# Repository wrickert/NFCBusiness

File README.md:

# NFCBusiness
## Overview
In order to stand out to potential employers I wanted to create my own variation on the PCB business card. I wanted my badge to do more than just look intresting. However, batteries are bulky and expensive. With the sheer number of phones equiped with Google pay/apple pay NFC in phones is becoming increasingly common. I think this makes NFC equiped PCB business cards a natural combination.

## RF430
This project uses a clever little chip, the RF430FRL154HCRGER. This chip is a variant on TI's MSP430. This one combines a NFC RF front end with a MSP430. We will be programming with a JTAG header and I will be building an accompanying POGO pin programming jig.

## D6 CharliePlexing Variant
There is a way to use CharliePlexing to drive seven LEDs with only two GPIO. This does not give you control of individual LEDs, but works in convient pairs for displaying dice values.<br>

## Programming Jig
Created a programming Jig that uses POGO pins, https://www.digikey.com/product-detail/en/mill-max-manufacturing-corp/0906-0-15-20-76-14-11-0/ED8180-ND <br>
This consists of two different PCBs that can all be stacked to reach the desired result<br>

## Status
1Jan2019 - Completed and ordered version 1<br>
17Jan2019 - IT WORKS! While the antenna leaves much to be desired it is good enough to register on my phone! Need to improve antenna and create programming jig.<br>
18Jan2019 - Fixed issues, created new PCB antenna, ordered version 2<br>
19Jan2019 - Found issue with V2, created V2a. Completed V1 Programming Jig and ordered from JLCPCB.<br>

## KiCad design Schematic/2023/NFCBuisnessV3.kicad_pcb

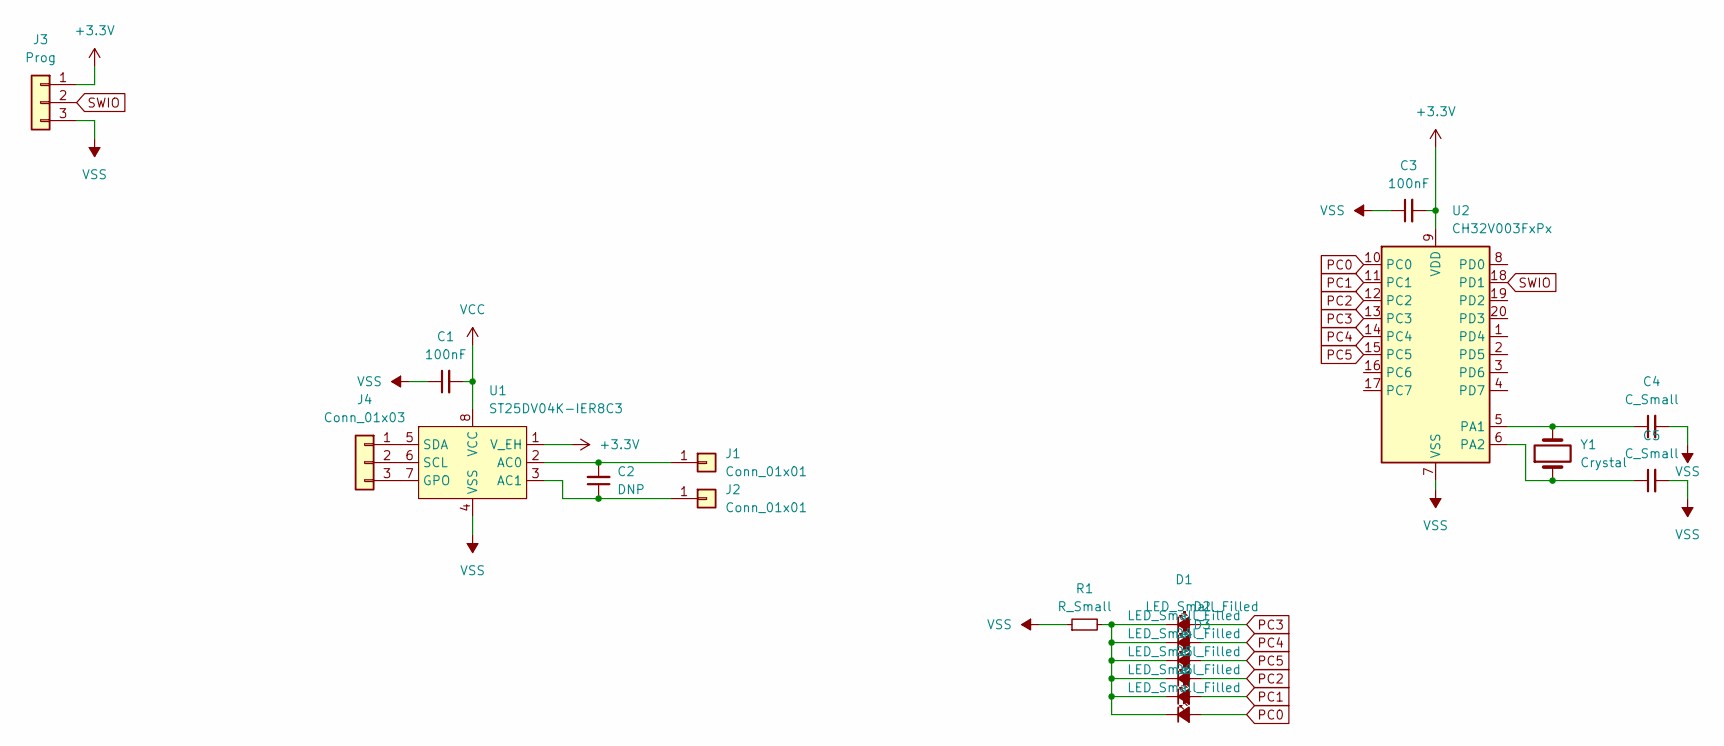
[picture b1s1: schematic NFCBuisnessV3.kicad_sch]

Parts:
C1, C3: 100nF; C_0805_2012Metric
C2: DNP; C_0805_2012Metric
C4, C5: C_Small; C_0805_2012Metric
D1, D2, D3, D4, D5, D6: LED_Small_Filled; LED_0805_2012Metric
J1, J2: Conn_01x01; NFCadapter
J3: Prog; PinHeader_1x03_P2.54mm_Vertical
J4: Conn_01x03; PinHeader_1x03_P2.54mm_Vertical
R1: R_Small; R_0805_2012Metric
U1: ST25DV04K-IER8C3; TSSOP_K-IER6T3_STM
U2: CH32V003FxPx; TSSOP-20_4.4x6.5mm_P0.65mm
Y1: Crystal; Crystal_SMD_2012-2Pin_2.0x1.2mm_HandSoldering

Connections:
+3.3V: C3.2, J3.1, U1.1 (V_EH), U2.9 (VDD)
unnamed: D1.1 (K), D2.1 (K), D3.1 (K), D4.1 (K), D5.1 (K), D6.1 (K), R1.2
unnamed: C2.2, J1.1, U1.2 (AC0)
unnamed: C2.1, J2.1, U1.3 (AC1)
unnamed: J4.1, U1.5 (SDA)
unnamed: J4.2, U1.6 (SCL)
unnamed: J4.3, U1.7 (GPO)
unnamed: C4.1, U2.5 (PA1), Y1.2
unnamed: C5.1, U2.6 (PA2), Y1.1
PC0: D6.2 (A), U2.10 (PC0)
PC1: D5.2 (A), U2.11 (PC1)
PC2: D4.2 (A), U2.12 (PC2)
PC3: D1.2 (A), U2.13 (PC3)
PC4: D2.2 (A), U2.14 (PC4)
PC5: D3.2 (A), U2.15 (PC5)
SWIO: J3.2, U2.18 (PD1)
VCC: C1.2, U1.8 (VCC)
VSS: C1.1, C3.1, C4.2, C5.2, J3.3, R1.1, U1.4 (VSS), U2.7 (VSS)

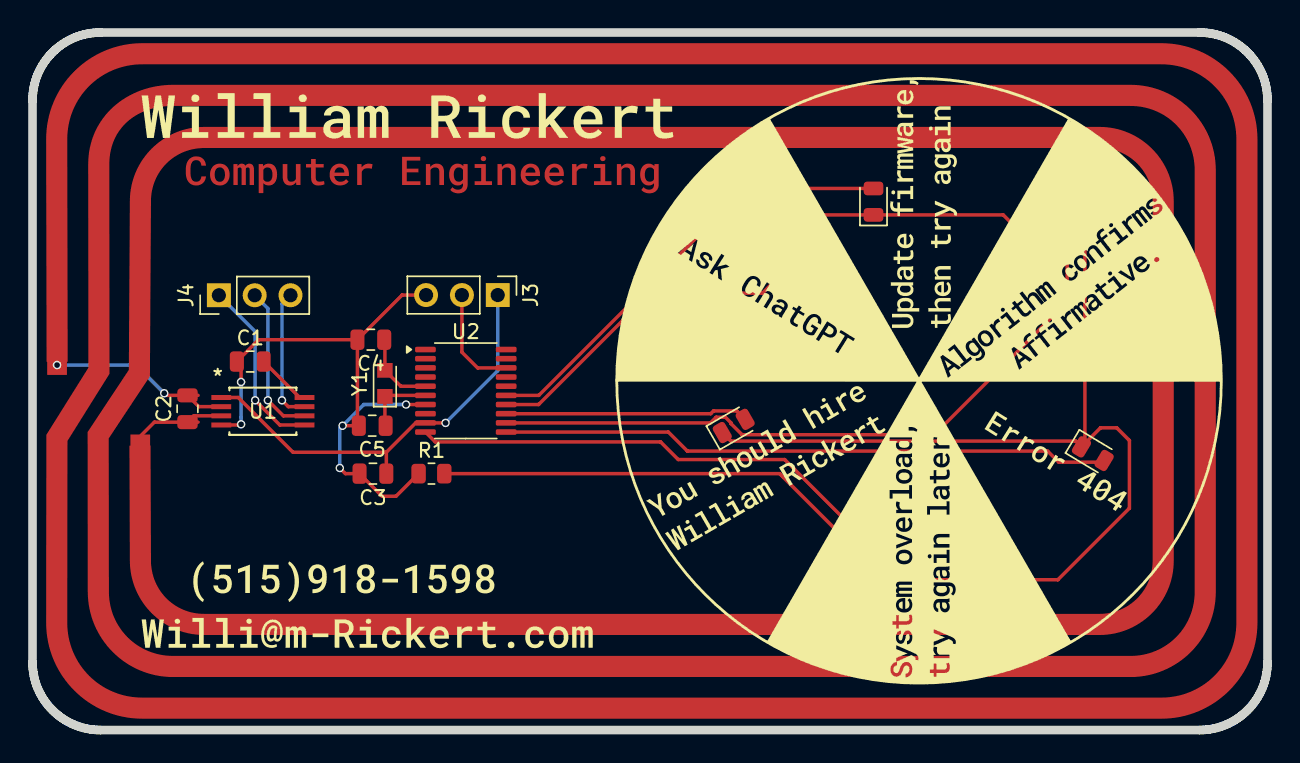
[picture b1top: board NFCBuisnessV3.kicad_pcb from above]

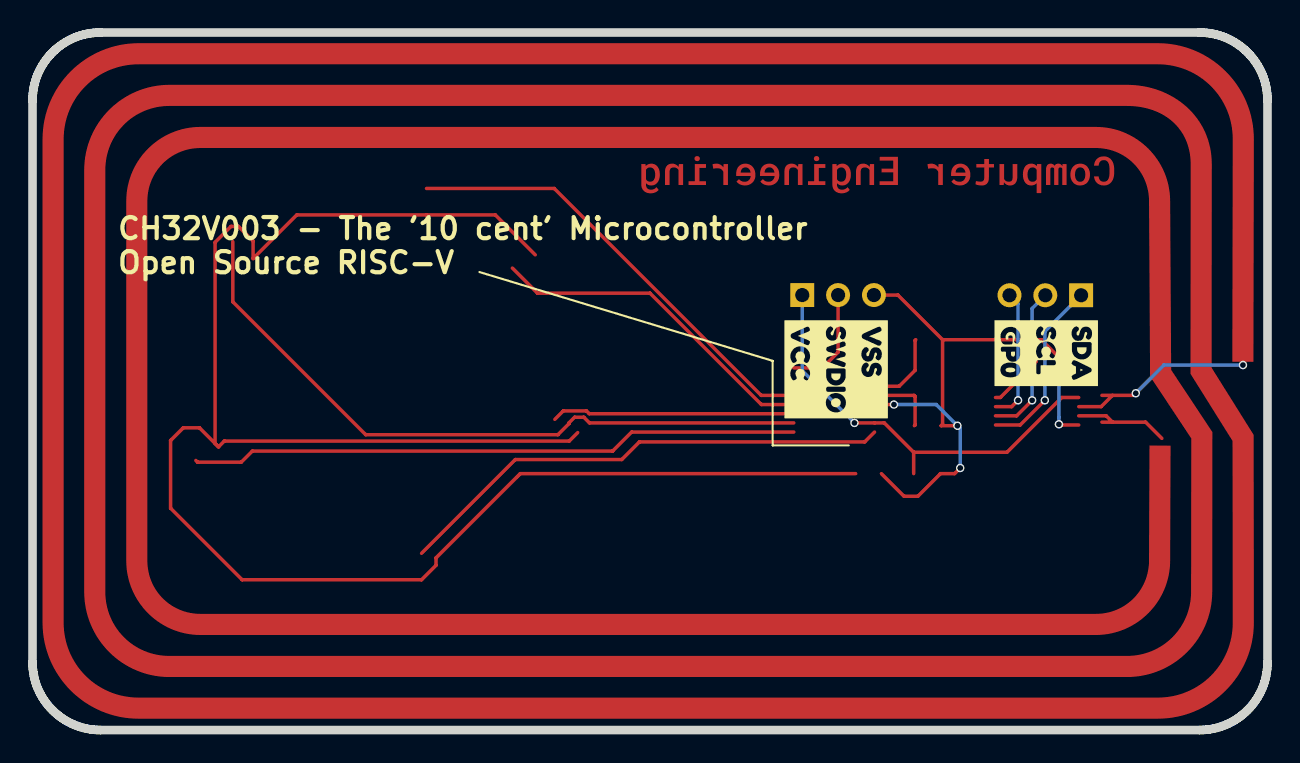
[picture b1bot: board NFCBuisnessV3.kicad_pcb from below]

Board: 2 copper layers, 87.6 x 49.5 mm, 21 parts (2 on the bottom side), 18 nets.

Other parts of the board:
kibuzzard-65E89835: G***; kibuzzard-65E89835
kibuzzard-65F9F6C6: G***; kibuzzard-65F9F6C6

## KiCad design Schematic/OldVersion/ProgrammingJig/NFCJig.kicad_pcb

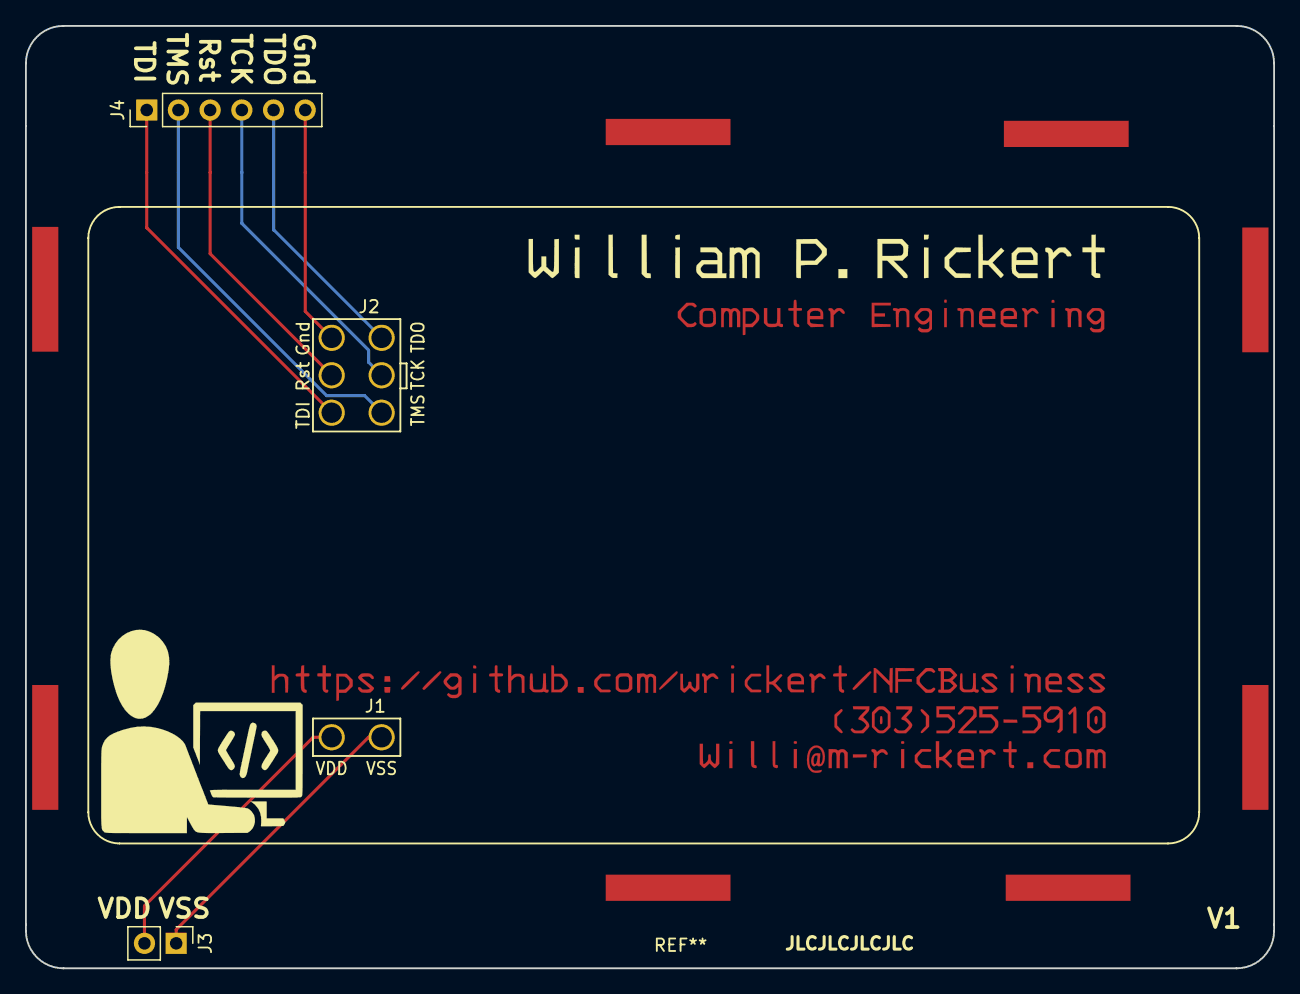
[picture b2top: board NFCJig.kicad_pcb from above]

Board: 2 copper layers, 100.0 x 75.5 mm, 4 parts (0 on the bottom side), 8 nets.

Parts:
J1: Power; PogoPwr
J2: JTAG; PogoJTAG
J3: Power; Pin_Header_Straight_1x02_Pitch2.54mm
J4: JTAG; Pin_Header_Straight_1x06_Pitch2.54mm

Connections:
unnamed: J1.1, J3.1
unnamed: J1.2, J3.2
unnamed: J2.1, J4.1
unnamed: J2.2, J4.2
unnamed: J2.3, J4.3
unnamed: J2.4, J4.4
unnamed: J2.5, J4.6
unnamed: J2.6, J4.5

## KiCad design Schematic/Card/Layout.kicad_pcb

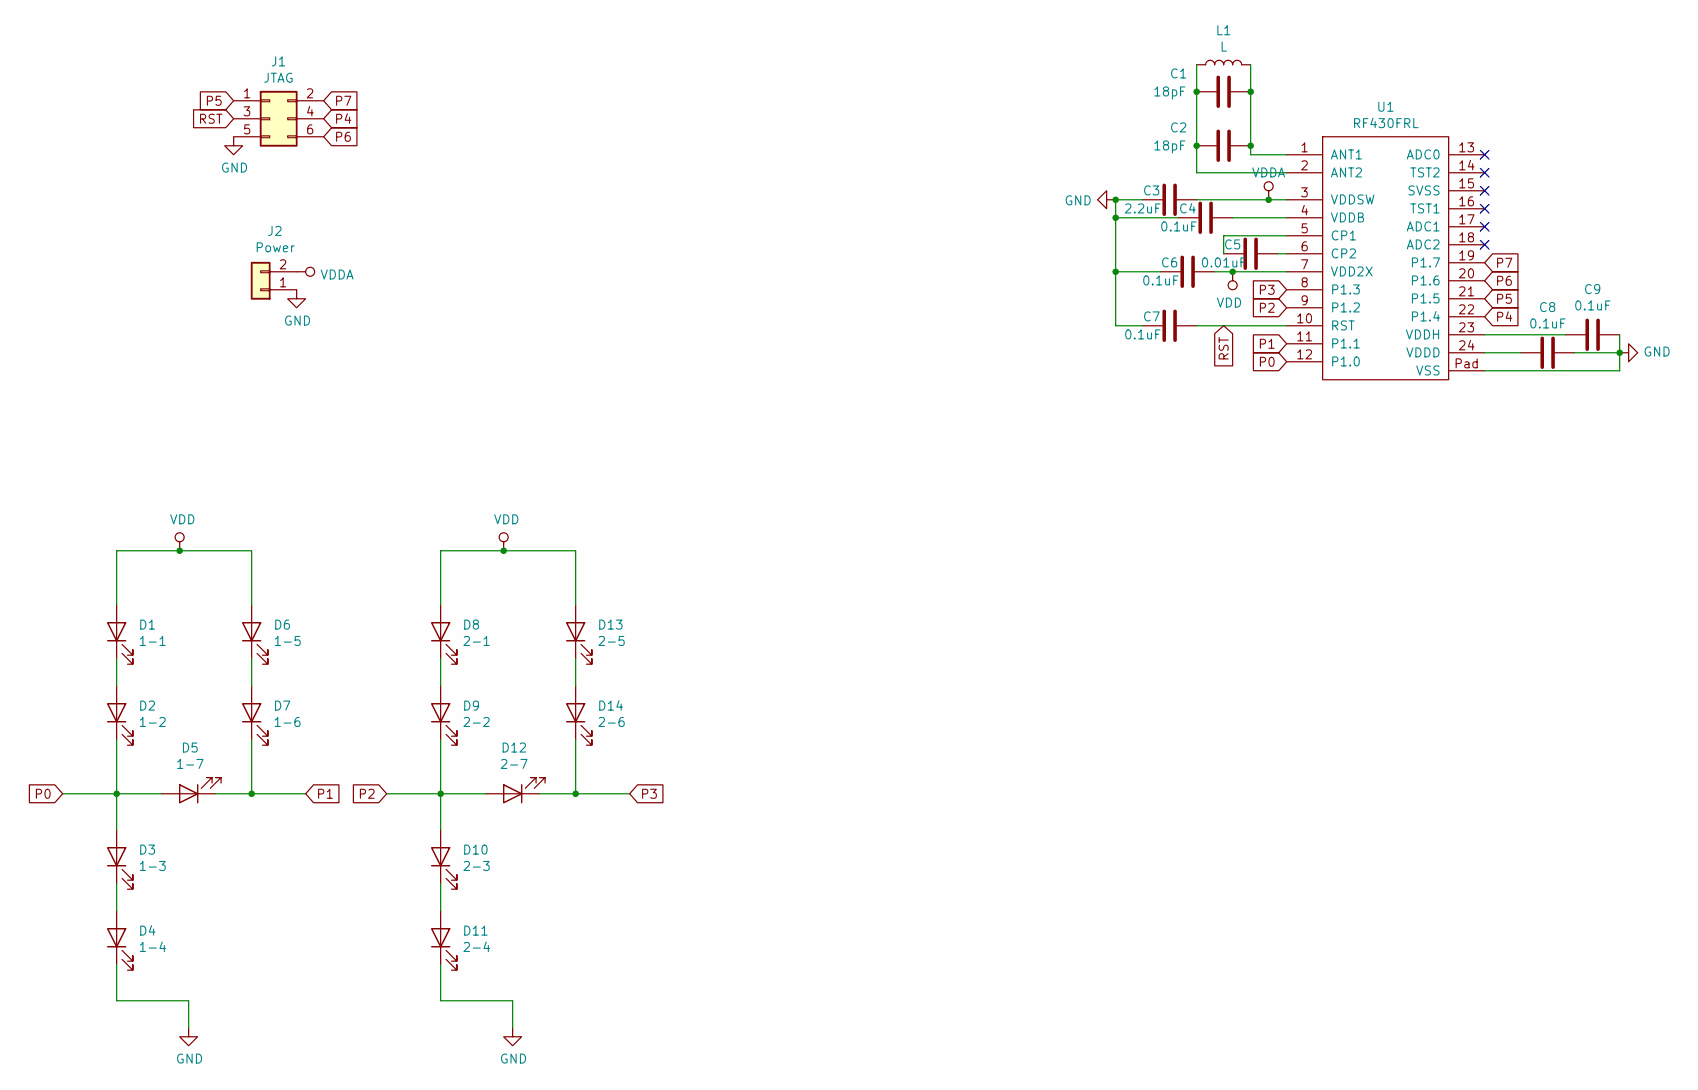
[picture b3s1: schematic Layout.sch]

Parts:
C1, C2: 18pF; C_0805
C3: 2.2uF; C_0805
C4, C6, C7, C8, C9: 0.1uF; C_0805
C5: 0.01uF; C_0805
D1: 1-1; LED_0805
D2: 1-2; LED_0805
D3: 1-3; LED_0805
D4: 1-4; LED_0805
D5: 1-7; LED_0805
D6: 1-5; LED_0805
D7: 1-6; LED_0805
D8: 2-1; LED_0805
D9: 2-2; LED_0805
D10: 2-3; LED_0805
D11: 2-4; LED_0805
D12: 2-7; LED_0805
D13: 2-5; LED_0805
D14: 2-6; LED_0805
J1: JTAG; Jtag
J2: Power; PwrPins
L1: L; Layout
U1: RF430FRL; QFN-24-1EP_4x4mm_Pitch0.5mm

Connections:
GND: C3.2, C4.2, C6.2, C7.2, C8.1, C9.1, D4.1 (K), D11.1 (K), J1.5, J2.1, U1.14 (TST2), U1.16 (TST1), U1.25, U1.Pad (VSS); also elsewhere on the board
unnamed 1: C1.1, C2.1, L1.2, U1.1 (ANT1); also elsewhere on the board
unnamed 2: C1.2, C2.2, L1.1, U1.2 (ANT2); also elsewhere on the board
unnamed: C4.1, U1.4 (VDDB)
unnamed: C5.1, U1.6 (CP2)
unnamed: C5.2, U1.5 (CP1)
unnamed: C8.2, U1.24 (VDDD)
unnamed: C9.2, U1.23 (VDDH)
unnamed 8: U1.17 (ADC1); also elsewhere on the board
unnamed: D1.1 (K), D2.2 (A)
unnamed: D3.1 (K), D4.2 (A)
unnamed: D6.1 (K), D7.2 (A)
unnamed: D8.1 (K), D9.2 (A)
unnamed: D10.1 (K), D11.2 (A)
unnamed: D13.1 (K), D14.2 (A)
unnamed 15: U1.15 (SVSS); also elsewhere on the board
P0: D2.1 (K), D3.2 (A), D5.2 (A), U1.12 (P1.0)
P1: D5.1 (K), D7.1 (K), U1.11 (P1.1)
P2: D9.1 (K), D10.2 (A), D12.2 (A), U1.9 (P1.2)
P3: D12.1 (K), D14.1 (K), U1.8 (P1.3)
P4: J1.4, U1.22 (P1.4)
P5: J1.1, U1.21 (P1.5)
P6: J1.6, U1.20 (P1.6)
P7: J1.2, U1.19 (P1.7)
RST: C7.1, J1.3, U1.10 (RST)
VDD: C6.1, D1.2 (A), D6.2 (A), D8.2 (A), D13.2 (A), U1.7 (VDD2X)
VDDA: C3.1, J2.2, U1.3 (VDDSW)

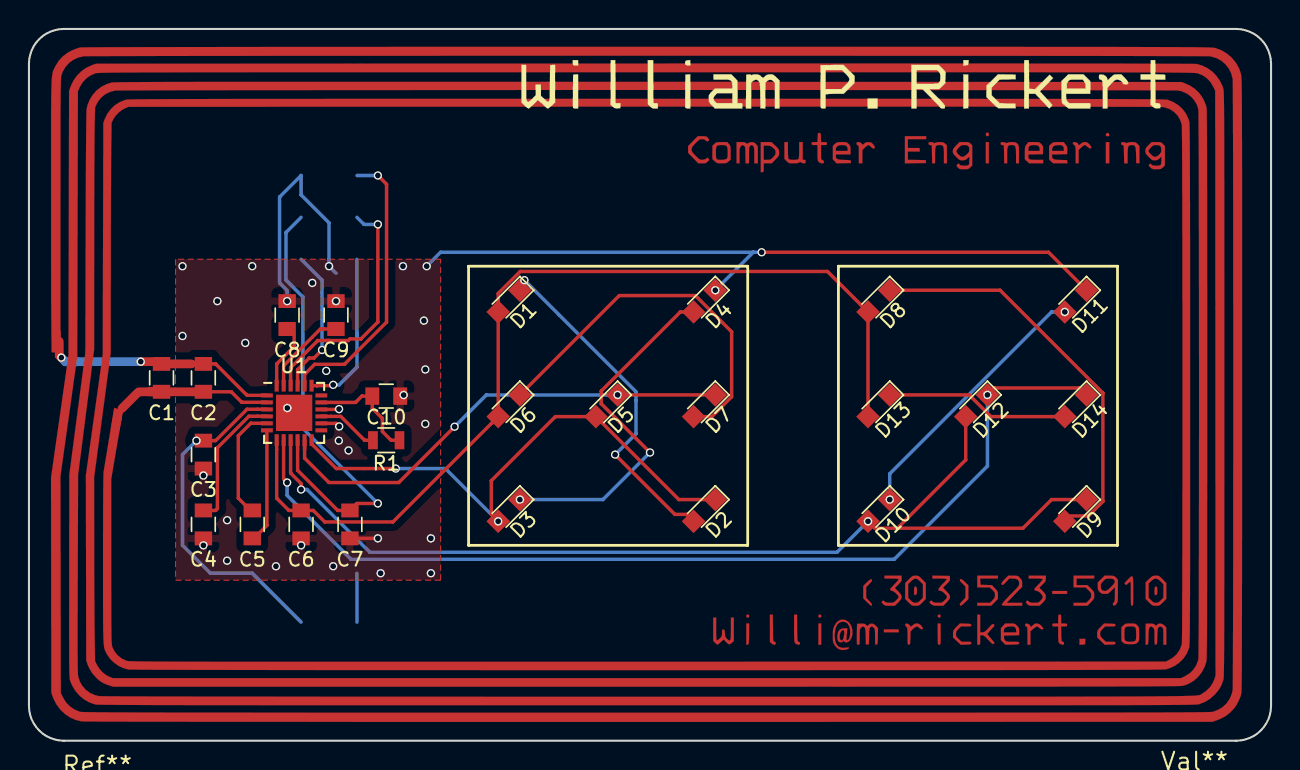
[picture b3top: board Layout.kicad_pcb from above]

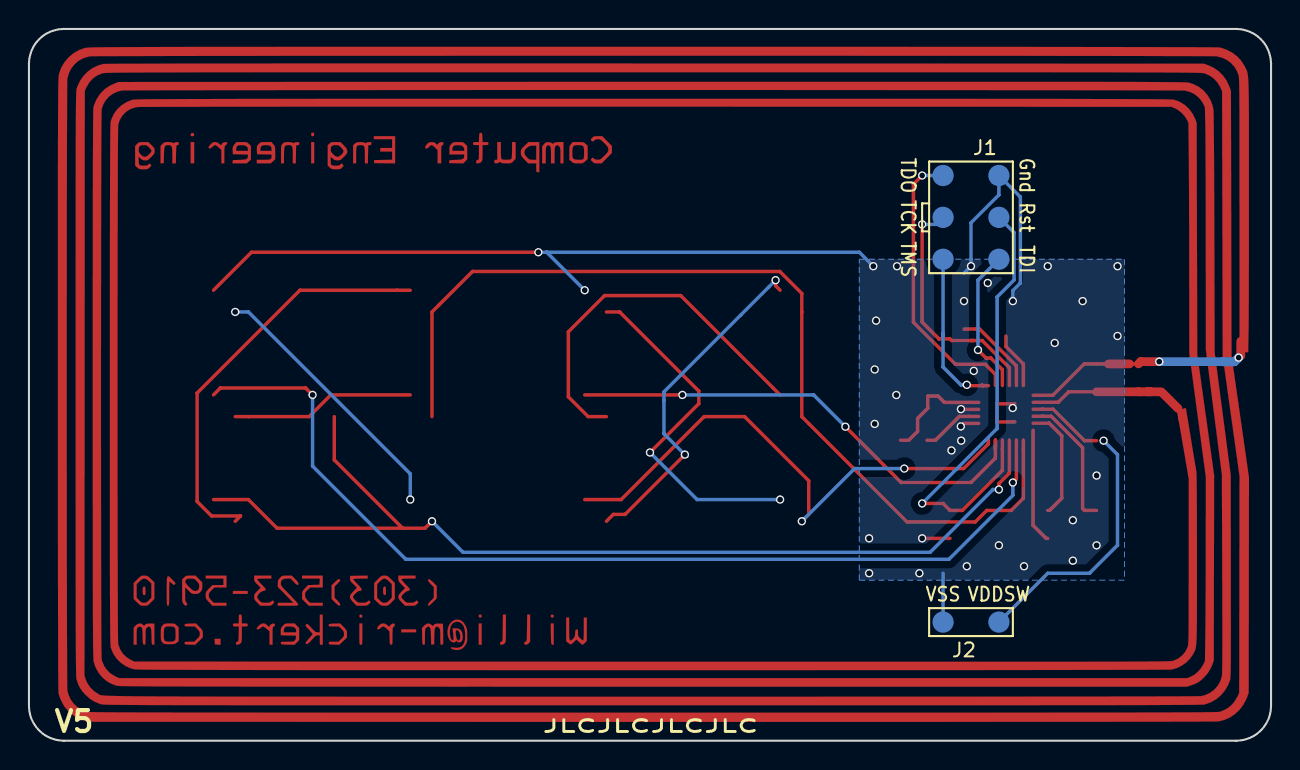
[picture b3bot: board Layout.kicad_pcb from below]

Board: 2 copper layers, 89.0 x 51.0 mm, 29 parts (2 on the bottom side), 27 nets.

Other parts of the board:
C10: 1uF; C_0805
R1: 100k; R_0805
Ref**: Val**; Layout-v2

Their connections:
GND: C10.1; also elsewhere on the board
unnamed 1: Ref**.1; also elsewhere on the board
unnamed 2: Ref**.2; also elsewhere on the board
unnamed 8: C10.2, R1.1; also elsewhere on the board
unnamed 15: R1.2; also elsewhere on the board

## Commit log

2018-12-23 Started project
2019-01-01 Antenna completed, working on schematics. About to begin programming jig
2019-01-01 Changing computers
2019-01-01 Housekeeping
2019-01-02 Finished and ordered V1
2019-01-02 Update readme and add jlcpcb renders
2019-01-07 Added JLC customer id location
2019-01-08 Changed programming footprint to use VDDSW
2019-01-19 Changed pcb antenna to match proper inductance
2019-01-19 Added to readme
2019-01-19 Played with graphics
2019-01-19 Fixed ground issue and cleaned up board
2019-01-19 Completed and ordered programming jig
2019-02-20 V3, changes may improve reading distance
2019-02-20 Removed drill file
2019-04-12 Added better ground plane
2024-03-06 Updated to 2023 info
2024-03-19 Updated for V2
2024-03-25 Ordered 2024 V2
